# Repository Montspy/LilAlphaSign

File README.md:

# LilAlphaSign
Little experiment at a WiFi connected RGB sign.
Background and "alert" animations can be triggered through HTTP requests.
User Manual: [here](extras/LilAlphaSign%20User%20Manual.pdf)

### Web interface

### Background animations

### "Alert" animations

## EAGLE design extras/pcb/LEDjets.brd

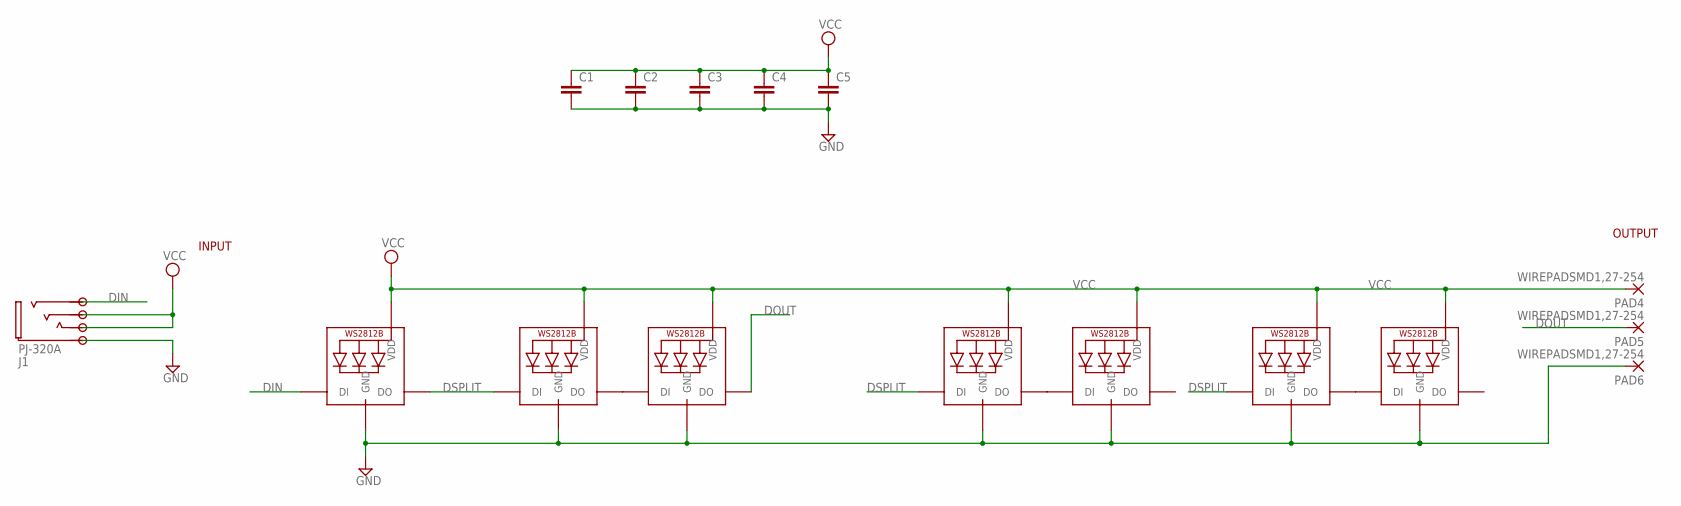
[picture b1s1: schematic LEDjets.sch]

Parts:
C1, C2, C3, C4, C5: C-EUC0805K; C0805K
J1: PJ-320A
LED1, LED2, LED3, LED4, LED5, LED6, LED7: WS2812B5050; WS2812B
PAD4, PAD5, PAD6: WIREPADSMD1,27-254; SMD1,27-2,54

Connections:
DIN: J1.2, LED1.4-DIN (DI)
DOUT: LED3.2-DOUT (DO), PAD5.1
DSPLIT: LED1.2-DOUT (DO), LED2.4-DIN (DI), LED4.4-DIN (DI), LED6.4-DIN (DI)
GND: C1.2, C2.2, C3.2, C4.2, C5.2, J1.5, LED1.3-GND (GND), LED2.3-GND (GND), LED3.3-GND (GND), LED4.3-GND (GND), LED5.3-GND (GND), LED6.3-GND (GND), LED7.3-GND (GND), PAD6.1
unnamed: LED2.2-DOUT (DO), LED3.4-DIN (DI)
unnamed: LED4.2-DOUT (DO), LED5.4-DIN (DI)
unnamed: LED6.2-DOUT (DO), LED7.4-DIN (DI)
VCC: C1.1, C2.1, C3.1, C4.1, C5.1, J1.3, J1.4, LED1.1-VDD (VDD), LED2.1-VDD (VDD), LED3.1-VDD (VDD), LED4.1-VDD (VDD), LED5.1-VDD (VDD), LED6.1-VDD (VDD), LED7.1-VDD (VDD), PAD4.1

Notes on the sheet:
INPUT
OUTPUT

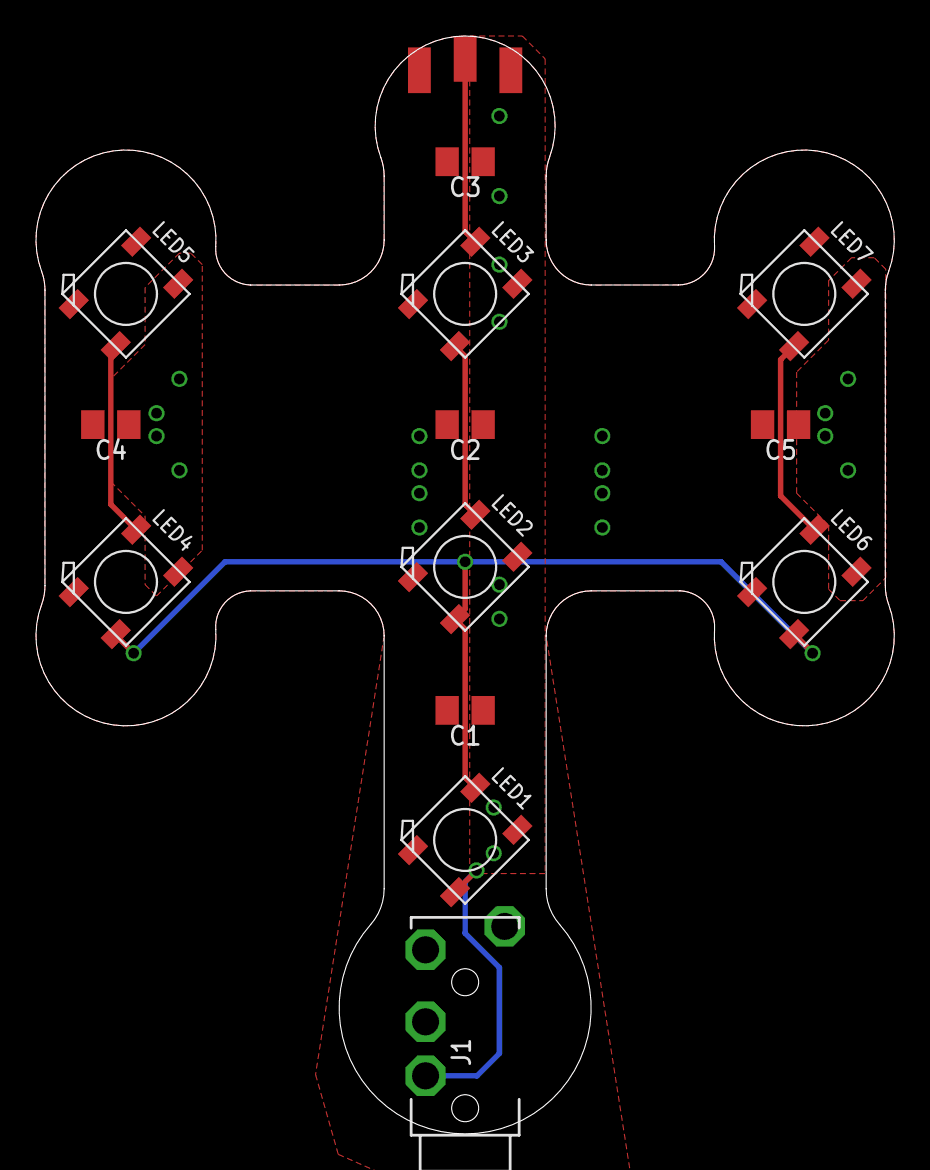
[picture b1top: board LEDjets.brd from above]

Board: 2 copper layers, 47.7 x 61.0 mm, 16 parts (0 on the bottom side), 8 nets.

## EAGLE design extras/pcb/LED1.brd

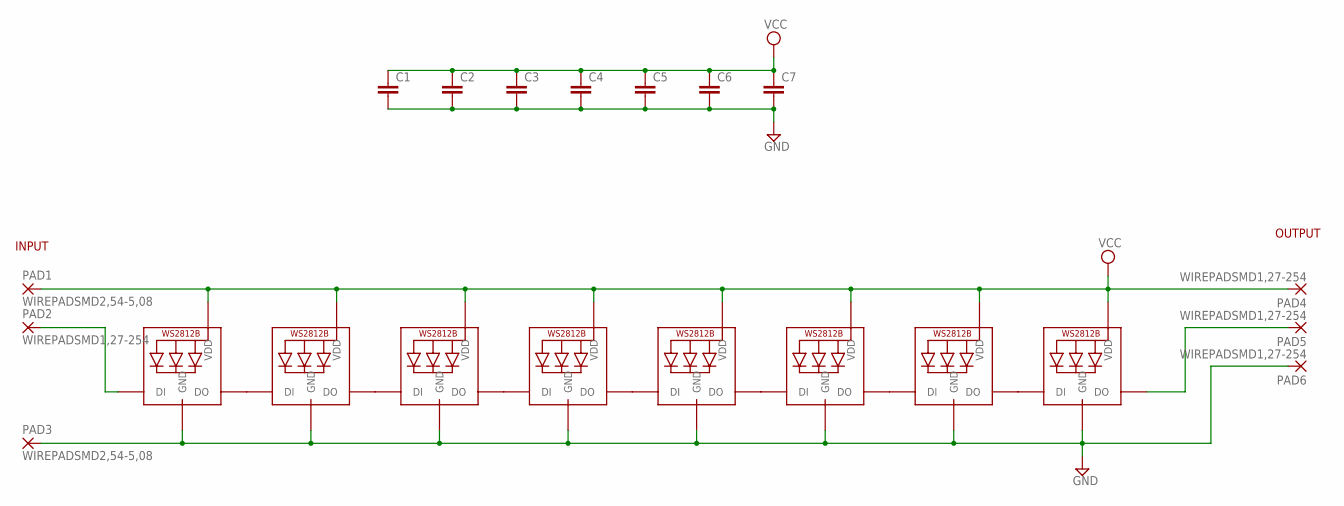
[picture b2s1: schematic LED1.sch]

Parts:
C1, C2, C3, C4, C5, C6, C7: C-EUC0805K; C0805K
LED1, LED2, LED3, LED4, LED5, LED6, LED7, LED8: WS2812B5050; WS2812B
PAD1, PAD3: WIREPADSMD2,54-5,08; SMD2,54-5,08
PAD2, PAD4, PAD5, PAD6: WIREPADSMD1,27-254; SMD1,27-2,54

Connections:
GND: C1.2, C2.2, C3.2, C4.2, C5.2, C6.2, C7.2, LED1.3-GND (GND), LED2.3-GND (GND), LED3.3-GND (GND), LED4.3-GND (GND), LED5.3-GND (GND), LED6.3-GND (GND), LED7.3-GND (GND), LED8.3-GND (GND), PAD3.1, PAD6.1
unnamed: LED1.2-DOUT (DO), LED2.4-DIN (DI)
unnamed: LED2.2-DOUT (DO), LED3.4-DIN (DI)
unnamed: LED3.2-DOUT (DO), LED4.4-DIN (DI)
unnamed: LED4.2-DOUT (DO), LED5.4-DIN (DI)
unnamed: LED5.2-DOUT (DO), LED6.4-DIN (DI)
unnamed: LED6.2-DOUT (DO), LED7.4-DIN (DI)
unnamed: LED1.4-DIN (DI), PAD2.1
unnamed: LED8.2-DOUT (DO), PAD5.1
unnamed: LED7.2-DOUT (DO), LED8.4-DIN (DI)
VCC: C1.1, C2.1, C3.1, C4.1, C5.1, C6.1, C7.1, LED1.1-VDD (VDD), LED2.1-VDD (VDD), LED3.1-VDD (VDD), LED4.1-VDD (VDD), LED5.1-VDD (VDD), LED6.1-VDD (VDD), LED7.1-VDD (VDD), LED8.1-VDD (VDD), PAD1.1, PAD4.1

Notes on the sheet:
INPUT
OUTPUT

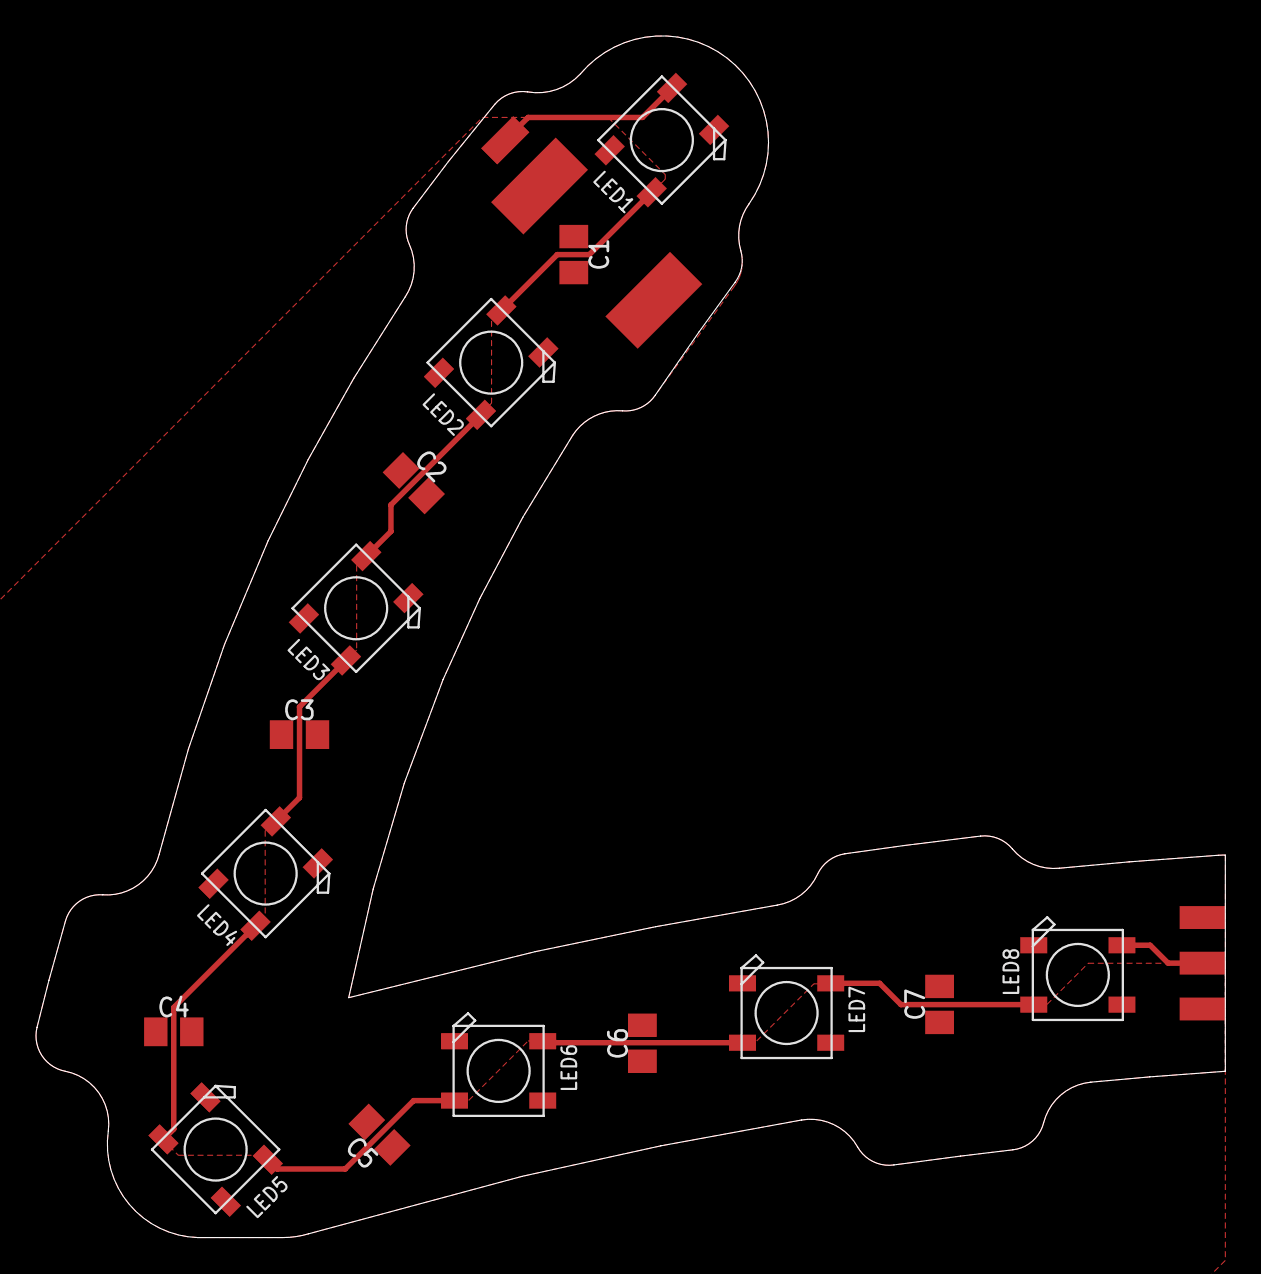
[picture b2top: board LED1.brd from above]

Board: 2 copper layers, 66.1 x 66.8 mm, 21 parts (0 on the bottom side), 11 nets.

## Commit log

2020-09-30 Moved cad to cad folder
2020-09-30 Updated cad for holders
2020-10-02 User Manual rev1
2020-10-02 Add user manual to readme
2021-08-12 Rename AlphaGamingSign.ino to LilAlphaSign.ino
    For Arduino IDE consistency
2021-08-12 Code cleanup from AlphaGaming logo to SamW logo
2021-08-12 Added PCB files and CAD files for SamW sign
2021-08-12 Added PCB dru and cam files
2021-08-14 Changed logo to SamW's rocket in web interface
2021-08-14 Moved cad files and added diffusers dxf/svg files
2021-08-14 gitignore some files
2021-08-15 Added 'grabby' fingers to help hold the front acrylic diffuser
2021-08-16 Modified 'intro' animation to match SamW rocket takeoff and updated default config.json to red colors
2021-08-16 Refactoring to use ESP32 board to resolve flickering issues when serving HTTP requests
2021-08-16 Fixed intro animation bug
2021-08-16 Color the rocket logo red in web interface
2021-08-16 Improved fit of Jets cover
2022-03-11 Add custom hostname
2022-12-04 add[www]: add reset wifi settings button
2022-12-04 chore[background]: adjust Beat animation
2022-12-04 fix[wifi]: fix device hostname
2022-12-04 add[cad]: add controller box STL files
